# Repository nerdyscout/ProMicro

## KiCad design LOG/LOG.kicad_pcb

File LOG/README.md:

# ProMicro_LOG 
This module can be mounted to an [Arduino Pro Mini](https://www.sparkfun.com/products/11113), [Arduino Nano](https://store.arduino.cc/arduino-nano), [Sparkfun Pro Micro](https://www.sparkfun.com/products/12587), or any other pincompatible MCU running with 3.3V. Depending on assembly it provides a RTC and/or µSD card slot.

## Documentation 
All files can be found on [Github](https://github.com/nerdyscout/ProMicro/tree/master/LOG).

### Schematic

### BoM
  * [interactiveHTMLBoM](https://nerdyscout.github.io/ProMicro/LOG/docs/bom/LOG-ibom.html)
  * [octopart](pcb/docs/bom/LOG-bom_octopart.csv)

## Hardware 
### Layout

### Gerbers
can be found within the Github [repository](pcb/gerbers).

## Code  (unless otherwise stated)
  * [SD CardInfo](examples/CardInfo/CardInfo.ino) 
  * [RTC SetAlarm](examples/SetAlarm/SetAlarm.ino)
  * [OpenLog](examples/OpenLog/OpenLog.ino)

Openlog seems to be tied to Serial0, but ProMicro does use Serial0 for USB and Serial1 internal. Therefore these can not easily be used.

## external
### Links
  * [hackaday.io](https://hackaday.io/project/171898-promicro)

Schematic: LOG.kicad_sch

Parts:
A1: Sparkfun_Pro_Micro
C1: 100n; C_0603_1608Metric
D1: LED; LED_0603_1608Metric
J1: Micro_SD_Card_Det; microSD_HC_Molex_104031-0811
JP1, JP2: Jumper_NO_Small; SolderJumper-2_P1.3mm_Open_RoundedPad1.0x1.5mm
JP3: SolderJumper_3_Bridged12; SolderJumper-3_P1.3mm_Bridged12_RoundedPad1.0x1.5mm_NumberL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
LOGO1: Logo_Open_Hardware_Small; OSHW-Symbol_6.7x6mm_SilkScreen
R1, R2, R3, R5, R6: 4k7; R_0603_1608Metric
R4: 1k; R_0603_1608Metric
TP1: VBAT; TestPoint_THTPad_D2.0mm_Drill1.0mm
U1: DS3231MZ; SOIC-8_3.9x4.9mm_P1.27mm

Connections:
+3V3: A1.21 (VCC), C1.1, J1.4, R2.1, R3.1, R5.1, R6.1, U1.2 (VCC)
BTN: A1.9 (D6/A7), R1.2
CIPO: A1.15 (MISO/D14), J1.7
COPI: A1.14 (MOSI/D16), J1.3
CS: J1.2, JP3.2 (C)
CS0: A1.13 (CS/D10), JP3.3 (B)
CS1: A1.12 (D9/A9), JP3.1 (A)
GND: A1.3 (GND), A1.4 (GND), A1.23 (GND), C1.2, D1.1 (K), J1.6, J1.10, J1.11, U1.5 (GND)
INT: A1.10 (D7), JP2.2 (B)
unnamed: D1.2 (A), R4.2
unnamed: J1.9, R1.1
unnamed: JP1.1 (A), R3.2, U1.1 (32KHZ)
unnamed: JP2.1 (A), R2.2, U1.3 (~INT/SQW)
unnamed: TP1.1, U1.6 (VBAT)
PWM: A1.8 (D5), JP1.2 (B)
SCK: A1.16 (SCK/D15), J1.5, R4.1
SCL: A1.6 (SCL/D3), R5.2, U1.8 (SCL)
SDA: A1.5 (SDA/D2), R6.2, U1.7 (SDA)
~RST: A1.22 (~RESET), U1.4 (~RST)

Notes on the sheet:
TDI
TD0
TMS
TCK

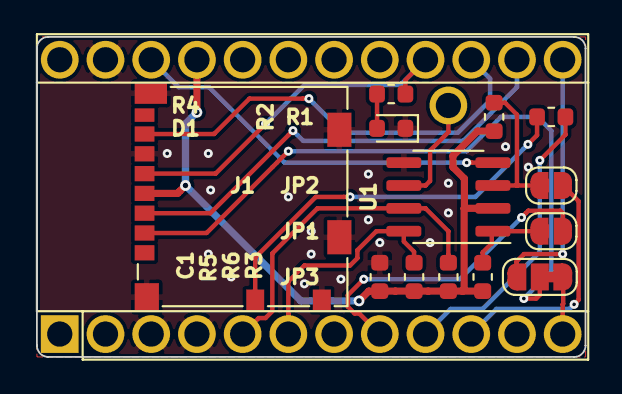
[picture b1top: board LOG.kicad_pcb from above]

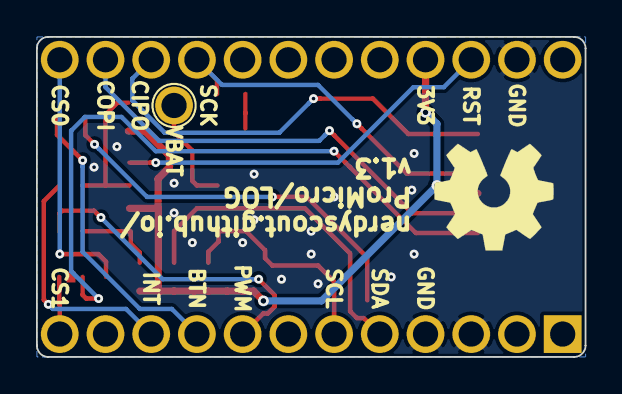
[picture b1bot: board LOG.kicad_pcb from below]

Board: 2 copper layers, 30.5 x 17.8 mm, 16 parts (2 on the bottom side), 19 nets.

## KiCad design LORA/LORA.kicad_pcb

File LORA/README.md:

:warning:
PCB currently not working! most likely some issue in the HF circuit.

# ProMicro_LORA 
This module can be mounted to an [Arduino Pro Mini](https://www.sparkfun.com/products/11113), [Arduino Nano](https://store.arduino.cc/arduino-nano), [Sparkfun Pro Micro](https://www.sparkfun.com/products/12587), or any other pincompatible MCU running with 3.3V. Manufacturing this PCB with 0.8mm thickness allows to mount a GPS module onto its back.

## Documentation 
All files can be found on [Github](https://github.com/nerdyscout/ProMicro/tree/master/LORA).

### Schematic

### BoM
  * [interactiveHTMLBoM](https://nerdyscout.github.io/ProMicro/LORA/docs/bom/LORA-ibom.html)
  * [octopart](pcb/docs/bom/LORA-bom_octopart.csv)

## Hardware 
### Layout

### Gerbers
can be found within the Github [repository](pcb/gerbers).

## Code  (unless otherwise stated)
 * [SX1276](examples/SX1276/SX1276.ino)

## external
### Links
  * [hackaday.io](https://hackaday.io/project/171898-promicro)

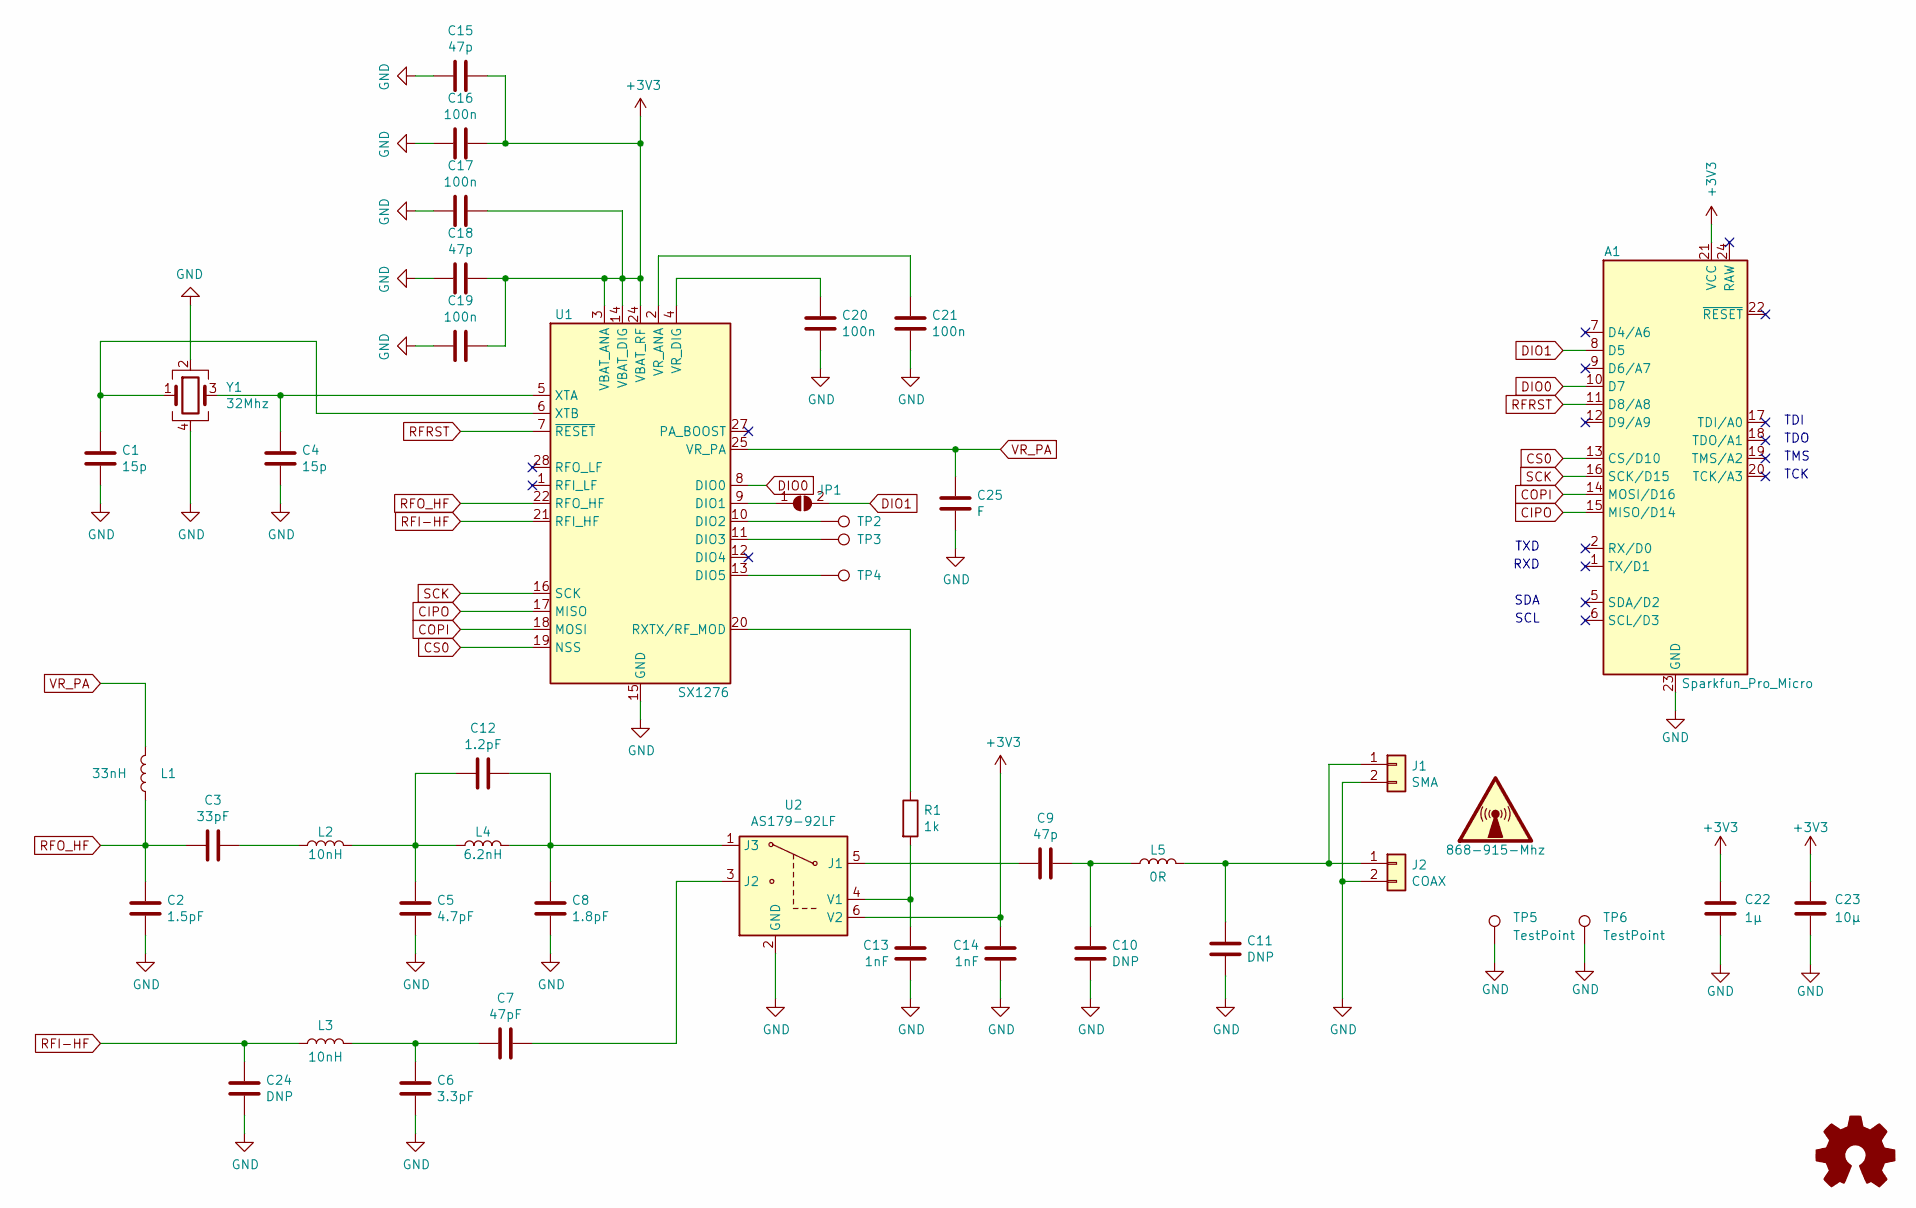
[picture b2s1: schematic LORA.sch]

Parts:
A1: Sparkfun_Pro_Micro
C1, C4: 15p; C_0402_1005Metric; MPN 0402CG150J500NT; LCSC# C1548
C2: 1.5pF; C_0402_1005Metric; MPN 0402CG1R5C500NT; LCSC# C1552
C3: 33pF; C_0402_1005Metric; MPN 0402CG330J500NT; LCSC# C1562
C5: 4.7pF; C_0402_1005Metric; MPN 0402CG4R7C500NT; LCSC# C1569
C6: 3.3pF; C_0402_1005Metric; MPN 0402CG3R3C500NT; LCSC# C1565
C7: 47pF; C_0402_1005Metric; MPN 0402CG470J500NT; LCSC# C1567
C8: 1.8pF; C_0402_1005Metric
C9, C15, C18: 47p; C_0402_1005Metric; MPN 0402CG470J500NT; LCSC# C1567
C10, C11, C24: DNP; C_0402_1005Metric
C12: 1.2pF; C_0402_1005Metric; MPN CL05C1R2BB5NNNC; LCSC# C159809
C13, C14: 1nF; C_0402_1005Metric; MPN 0402B102K500NT; LCSC# C1523
C16, C17, C19, C20, C21: 100n; C_0402_1005Metric; MPN CL05B104KO5NNNC; LCSC# C1525
C22: 1µ; C_0402_1005Metric; MPN CL05A105KA5NQNC; LCSC# C52923
C23: 10µ; C_0603_1608Metric; MPN CL05A106MQ5NUNC; LCSC# C15525
C25: F; C_0402_1005Metric
J1: SMA; U.FL_Hirose_U.FL-R-SMT-1_Vertical
J2: COAX; SMA_Samtec_SMA-J-P-H-ST-EM1_EdgeMount
JP1: SolderJumper_2_Open; SolderJumper-2_P1.3mm_Open_RoundedPad1.0x1.5mm
L1: 33nH; L_0402_1005Metric; MPN HK100533NJ-T; LCSC# C87193
L2, L3: 10nH; L_0402_1005Metric; MPN SDCL1005C10NJTDF; LCSC# C27147
L4: 6.2nH; L_0402_1005Metric; MPN MLG1005S6N2ST000; LCSC# C87534
L5: 0R; L_0402_1005Metric; MPN 0402WGF0000TCE; LCSC# C17168
LOGO1: Logo_Open_Hardware_Small; OSHW-Symbol_6.7x6mm_SilkScreen
R1: 1k; R_0402_1005Metric; MPN 0402WGF1001TCE; LCSC# C11702
TP2: DIO2; TestPoint_Pad_D1.0mm
TP3: DIO3; TestPoint_Pad_D1.0mm
TP4: DIO5; TestPoint_Pad_D1.0mm
TP5, TP6: TestPoint; TestPoint_Pad_1.5x1.5mm
U1: SX1276; QFN-28-1EP_6x6mm_P0.65mm_EP4.8x4.8mm
U2: AS179-92LF; SOT-363_SC-70-6; MPN AS179-92LF; LCSC# C83422
Y1: 32Mhz; Crystal_SMD_SeikoEpson_FA238V-4Pin_3.2x2.5mm; MPN X1E000021016300; LCSC# C91742

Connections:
+3V3: A1.21 (VCC), C14.1, C15.1, C16.2, C17.2, C18.1, C19.2, C22.1, C23.1, U1.3 (VBAT_ANA), U1.14 (VBAT_DIG), U1.24 (VBAT_RF), U2.6 (V2)
CIPO: A1.15 (MISO/D14), U1.17 (MISO)
COPI: A1.14 (MOSI/D16), U1.18 (MOSI)
CS0: A1.13 (CS/D10), U1.19 (NSS)
DIO0: A1.10 (D7), U1.8 (DIO0)
DIO1: A1.8 (D5), JP1.2 (B)
GND: A1.3 (GND), A1.4 (GND), A1.23 (GND), C1.2, C2.1, C4.2, C5.2, C6.2, C8.2, C10.2, C11.2, C13.2, C14.2, C15.2, C16.1, C17.1, C18.2, C19.1, C20.2, C21.2, C22.2, C23.2, C24.2, C25.2, J1.2, J2.2, TP5.1, TP6.1, U1.15 (GND), U1.23 (GND), U1.26 (GND), U1.29 (GND), U2.2 (GND), Y1.2, Y1.4
unnamed: C3.1, L2.1
unnamed: C6.1, C7.2, L3.2
unnamed: C9.1, C10.1, L5.1
unnamed: C5.1, C12.2, L2.2, L4.1
unnamed: C11.1, J1.1, J2.1, L5.2
unnamed: JP1.1 (A), U1.9 (DIO1)
unnamed: TP2.1, U1.10 (DIO2)
unnamed: TP3.1, U1.11 (DIO3)
unnamed: TP4.1, U1.13 (DIO5)
unnamed: R1.1, U1.20 (RXTX/RF_MOD)
unnamed: C21.1, U1.2 (VR_ANA)
unnamed: C20.1, U1.4 (VR_DIG)
unnamed: C4.1, U1.5 (XTA), Y1.3
unnamed: C1.1, U1.6 (XTB), Y1.1
unnamed: C9.2, U2.5 (J1)
unnamed: C7.1, U2.3 (J2)
unnamed: C8.1, C12.1, L4.2, U2.1 (J3)
unnamed: C13.1, R1.2, U2.4 (V1)
RFI-HF: C24.1, L3.1, U1.21 (RFI_HF)
RFO_HF: C2.2, C3.2, L1.1, U1.22 (RFO_HF)
RFRST: A1.11 (D8/A8), U1.7 (~RESET)
SCK: A1.16 (SCK/D15), U1.16 (SCK)
VR_PA: C25.1, L1.2, U1.25 (VR_PA)

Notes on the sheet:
TDI
TDO
TMS
TCK
RXD
TXD
SDA
SCL

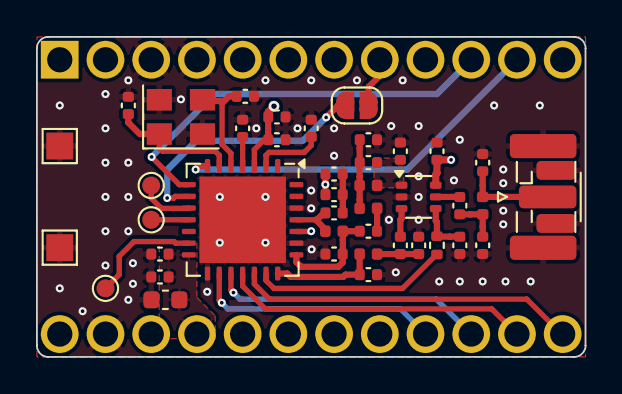
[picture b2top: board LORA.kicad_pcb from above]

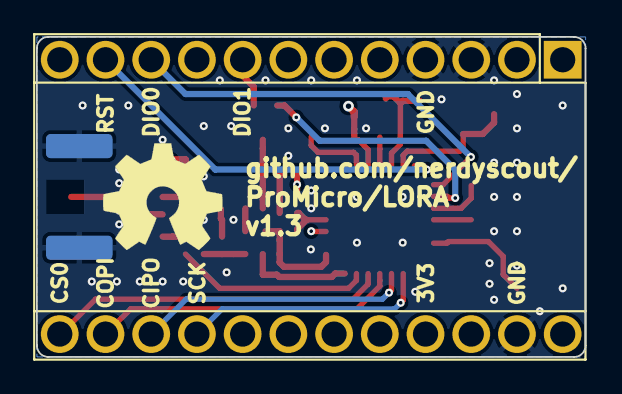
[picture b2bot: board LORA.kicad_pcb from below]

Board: 4 copper layers, 30.5 x 17.8 mm, 44 parts (2 on the bottom side), 30 nets.

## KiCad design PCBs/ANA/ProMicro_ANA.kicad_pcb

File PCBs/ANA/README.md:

# ProMicro_ANA
This module can be mounted to an [Arduino Pro Mini](https://www.sparkfun.com/products/11113), [Arduino Nano](https://store.arduino.cc/arduino-nano), [Sparkfun Pro Micro](https://www.sparkfun.com/products/12587), or any other pincompatible MCU running with 3.3V. Depending on assembly it provides a RTC and/or µSD card slot.

## Documentation
All files can be found on [Github](https://github.com/nerdyscout/ProMicro_ANA).

### Schematic

### Layout

### BoM
  * [interactiveHTMLBoM](https://nerdyscout.github.io/ProMicro_ANA/docs/bom/ProMicro_ANA.html))
  * [kicost](docs/bom/ProMicro_ANA.xlsx)
  * [csv](docs/bom/ProMicro_ANA.csv)

## Gerbers
can be found within the Github [repository](https://github.com/nerdyscout/ProMicro_ANA/tree/master/gerbers).

## Code
| | 1 | 2 |
| --- | --- | --- |
| Sparkfun ProMicro | [a](l) | [b](l) |
| Arduino Mini | [a](l)<br>[c](l) | [b](l) |

## Links
  * [hackaday.io](https://hackaday.io/project/171898-promicro)

## License
Copyright Stefan Herold 2020

This documentation describes Open Hardware and is licensed under the CERN OHL v.1.2.

You may redistribute and modify this documentation under the terms of the CERN OHL v.1.2. (http://ohwr.org/cernohl). This documentation is distributed WITHOUT ANY EXPRESS OR IMPLIED WARRANTY, INCLUDING OF MERCHANTABILITY, SATISFACTORY QUALITY AND FITNESS FOR A PARTICULAR PURPOSE. Please see the CERN OHL v.1.2 for applicable conditions

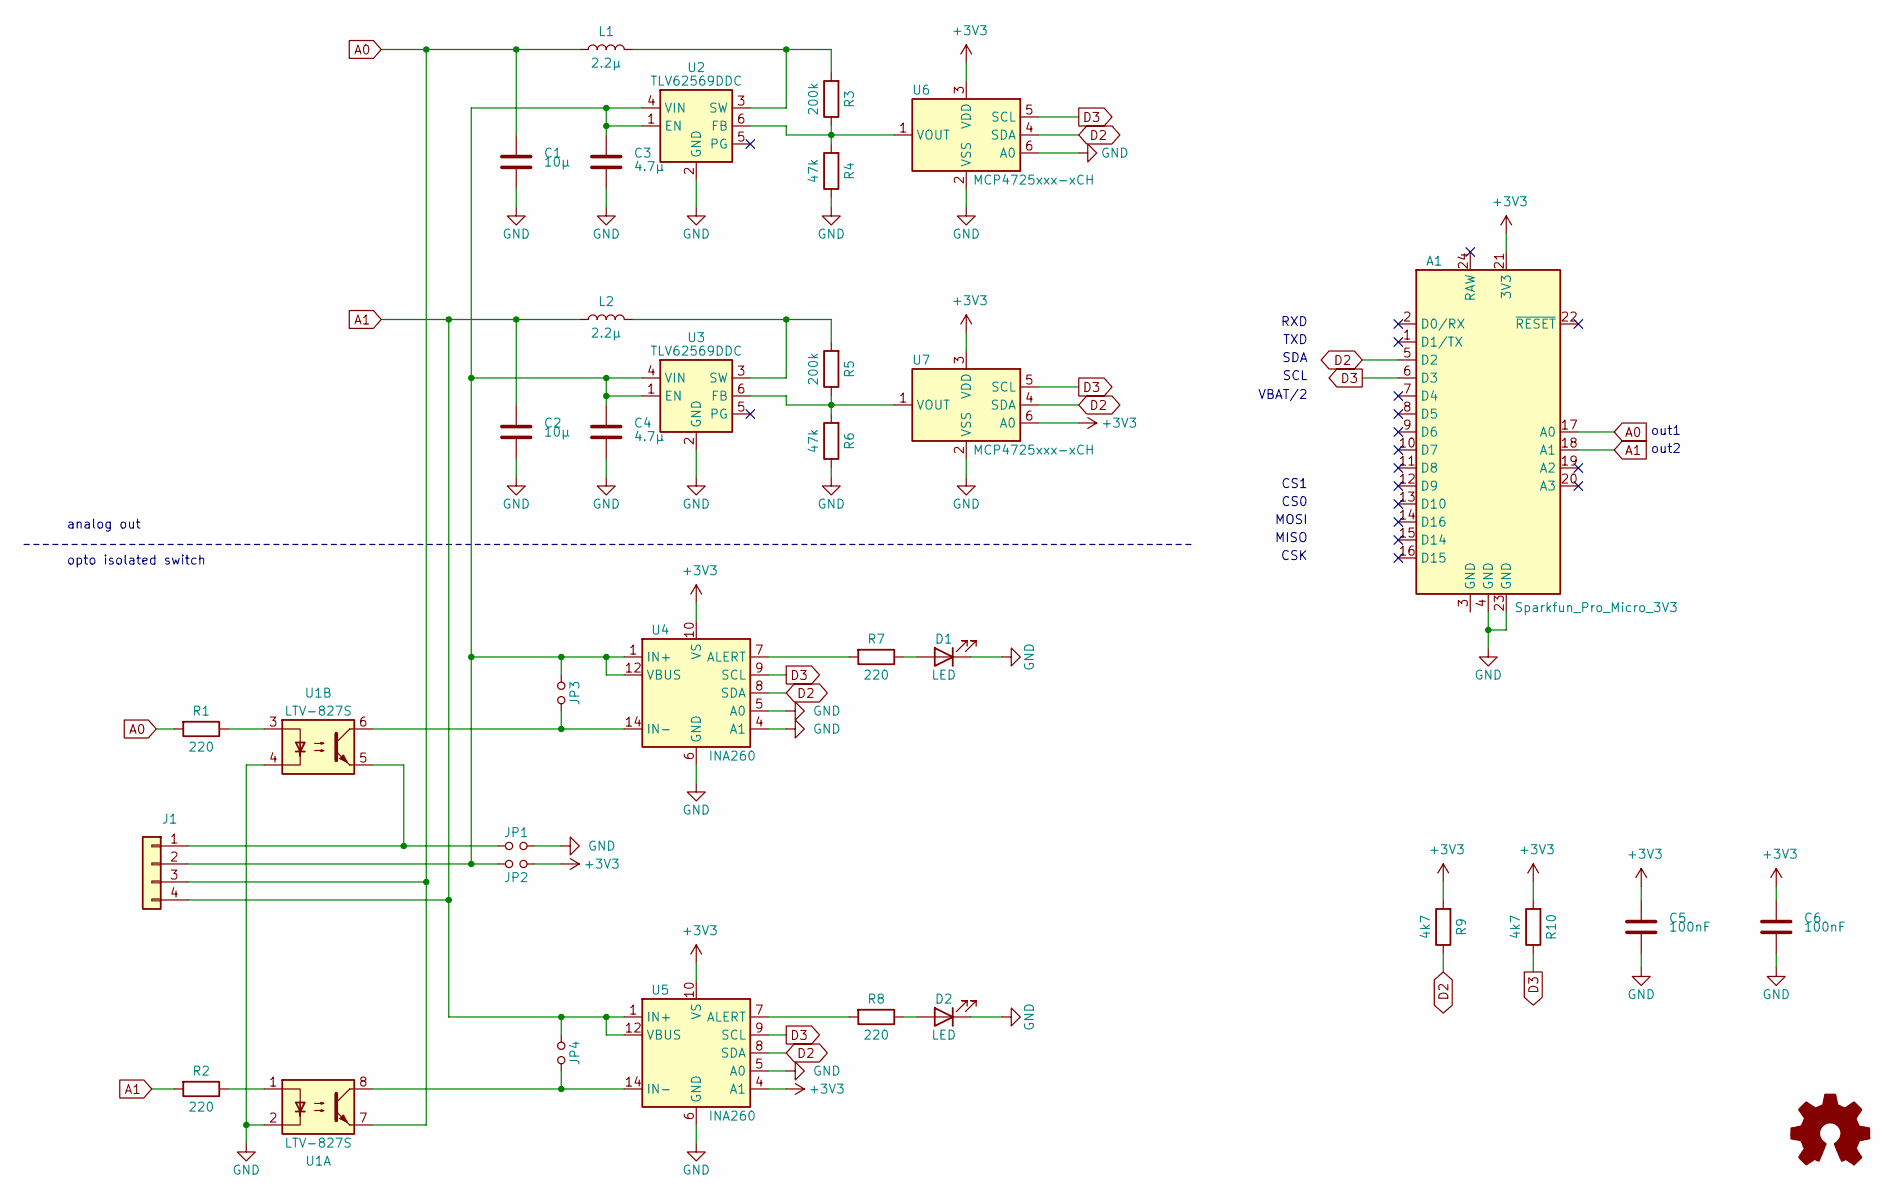
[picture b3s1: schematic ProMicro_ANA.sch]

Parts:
A1: Sparkfun_Pro_Micro_3V3; Sparkfun_Pro_Micro
C1, C2: 10µ; C_0603_1608Metric
C3, C4: 4.7µ; C_0603_1608Metric
C5, C6: 100nF; C_0603_1608Metric
D1, D2: LED; LED_0603_1608Metric
J1: Conn_01x04; TerminalBlock_Phoenix_MPT-0,5-4-2.54_1x04_P2.54mm_Horizontal
JP1, JP2, JP3, JP4: Jumper_NO_Small; SolderJumper-2_P1.3mm_Open_RoundedPad1.0x1.5mm
L1, L2: 2.2µ; L_Bourns-SRN4018
LOGO1: Logo_Open_Hardware_Small; OSHW-Symbol_6.7x6mm_SilkScreen
R1, R2, R7, R8: 220; R_0603_1608Metric
R3, R5: 200k; R_0603_1608Metric
R4, R6: 47k; R_0603_1608Metric
R9, R10: 4k7; R_0603_1608Metric
U1: LTV-827S; SMDIP-8_W9.53mm
U2, U3: TLV62569DDC; SOT-23-6
U4, U5: INA260; TSSOP-16_4.4x5mm_P0.65mm
U6, U7: MCP4725xxx-xCH; SOT-23-6

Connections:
+3V3: A1.21 (3V3), C5.1, C6.1, JP2.2, R9.2, R10.2, U4.10 (VS), U5.4 (A1), U5.10 (VS), U6.3 (VDD), U7.3 (VDD), U7.6 (A0)
A0: A1.17 (A0), C1.1, J1.3, L1.1, R1.2, U1.7
A1: A1.18 (A1), C2.1, J1.4, JP4.1, L2.1, R2.2, U5.1 (IN+), U5.2 (IN+), U5.3 (IN+), U5.12 (VBUS)
D2: A1.5 (D2), R9.1, U4.8 (SDA), U5.8 (SDA), U6.4 (SDA), U7.4 (SDA)
D3: A1.6 (D3), R10.1, U4.9 (SCL), U5.9 (SCL), U6.5 (SCL), U7.5 (SCL)
GND: A1.4 (GND), A1.23 (GND), C1.2, C2.2, C3.2, C4.2, C5.2, C6.2, D1.1 (K), D2.1 (K), JP1.2, R4.1, R6.1, U1.2, U1.4, U2.2 (GND), U3.2 (GND), U4.4 (A1), U4.5 (A0), U4.6 (GND), U4.11 (GND), U5.5 (A0), U5.6 (GND), U5.11 (GND), U6.2 (VSS), U6.6 (A0), U7.2 (VSS)
unnamed: C3.1, C4.1, J1.2, JP2.1, JP3.1, U2.1 (EN), U2.4 (VIN), U3.1 (EN), U3.4 (VIN), U4.1 (IN+), U4.2 (IN+), U4.3 (IN+), U4.12 (VBUS)
unnamed: D1.2 (A), R7.1
unnamed: D2.2 (A), R8.1
unnamed: J1.1, JP1.1, U1.5
unnamed: JP3.2, U1.6, U4.14 (IN-), U4.15 (IN-), U4.16 (IN-)
unnamed: JP4.2, U1.8, U5.14 (IN-), U5.15 (IN-), U5.16 (IN-)
unnamed: L1.2, R3.2, U2.3 (SW)
unnamed: L2.2, R5.2, U3.3 (SW)
unnamed: R1.1, U1.3
unnamed: R2.1, U1.1
unnamed: R3.1, R4.2, U2.6 (FB), U6.1 (VOUT)
unnamed: R5.1, R6.2, U3.6 (FB), U7.1 (VOUT)
unnamed: R7.2, U4.7 (ALERT)
unnamed: R8.2, U5.7 (ALERT)

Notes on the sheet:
out1
out2
opto isolated switch
analog out
SCL
SDA
TXD
RXD
CSK
MISO
MOSI
CS0
CS1
VBAT/2

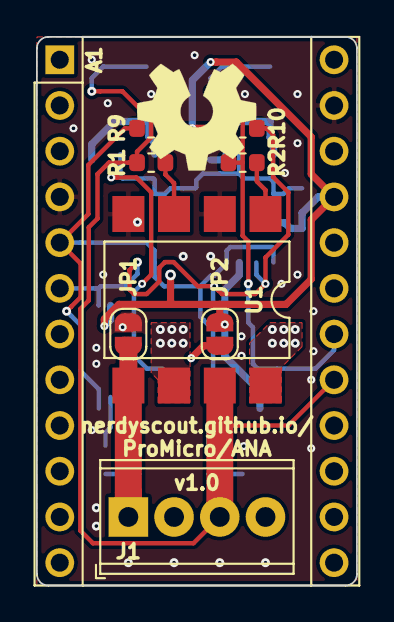
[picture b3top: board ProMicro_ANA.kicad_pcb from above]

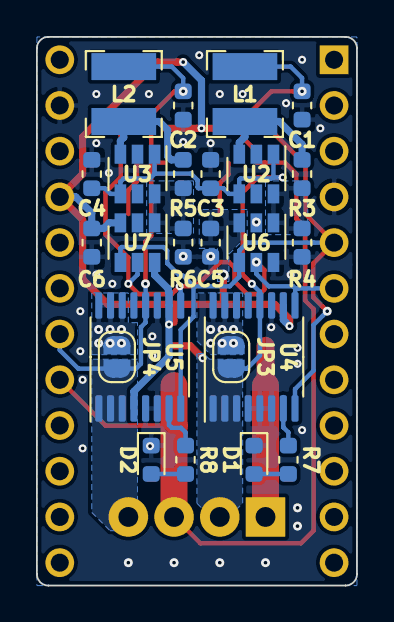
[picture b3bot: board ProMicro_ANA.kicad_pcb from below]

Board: 2 copper layers, 17.8 x 30.5 mm, 34 parts (24 on the bottom side), 20 nets.

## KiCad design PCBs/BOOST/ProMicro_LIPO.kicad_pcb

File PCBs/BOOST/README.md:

# ProMicro_LIPO
This module can be mounted, back on back, to any [Arduino Pro Mini](https://www.sparkfun.com/products/11113), [Arduino Nano](https://store.arduino.cc/arduino-nano) or [Sparkfun Pro Micro](https://www.sparkfun.com/products/12587) running with 3.3V. While the controller gets externally powered the LiPo battery is charging, removing the cable the device keeps running on battery.

## Documentation
All files can be found on [Github](https://github.com/nerdyscout/ProMicro_LIPO).

### Schematic

### Layout

### BoM
  * [interactiveHTMLBoM](https://nerdyscout.github.io/ProMicro_LIPO/docs/BOM/ProMicro_LIPO.html)
  * [kicost](docs/BOM/ProMicro_LIPO.xlsx)
  * [csv](docs/BOM/ProMicro_LIPO.csv)

## Gerbers
can be found within the Github [repository](gerbers).

## Code
  * [Arduino Micro 3V3](examples/Arduino_Micro_LIPO/Arduino_Micro_LIPO.ino)
  * [Arduino Nano 3V3](examples/Arduino_Nano_LIPO/Arduino_Nano_LIPO.ino)
  * [Sparkfun Pro Micro 3V3](examples/Sparkfun_ProMicro_LIPO/Sparkfun_ProMicro_LIPO.ino)

## Links
  * [hackaday.io](https://hackaday.io/project/171898-promicro)

## Credits
  * [Adafruit PowerBoost 500 Basic](https://learn.adafruit.com/adafruit-powerboost)

## License
Copyright Stefan Herold 2020

This documentation describes Open Hardware and is licensed under the CERN OHL v.1.2.

You may redistribute and modify this documentation under the terms of the CERN OHL v.1.2. (http://ohwr.org/cernohl). This documentation is distributed WITHOUT ANY EXPRESS OR IMPLIED WARRANTY, INCLUDING OF MERCHANTABILITY, SATISFACTORY QUALITY AND FITNESS FOR A PARTICULAR PURPOSE. Please see the CERN OHL v.1.2 for applicable conditions

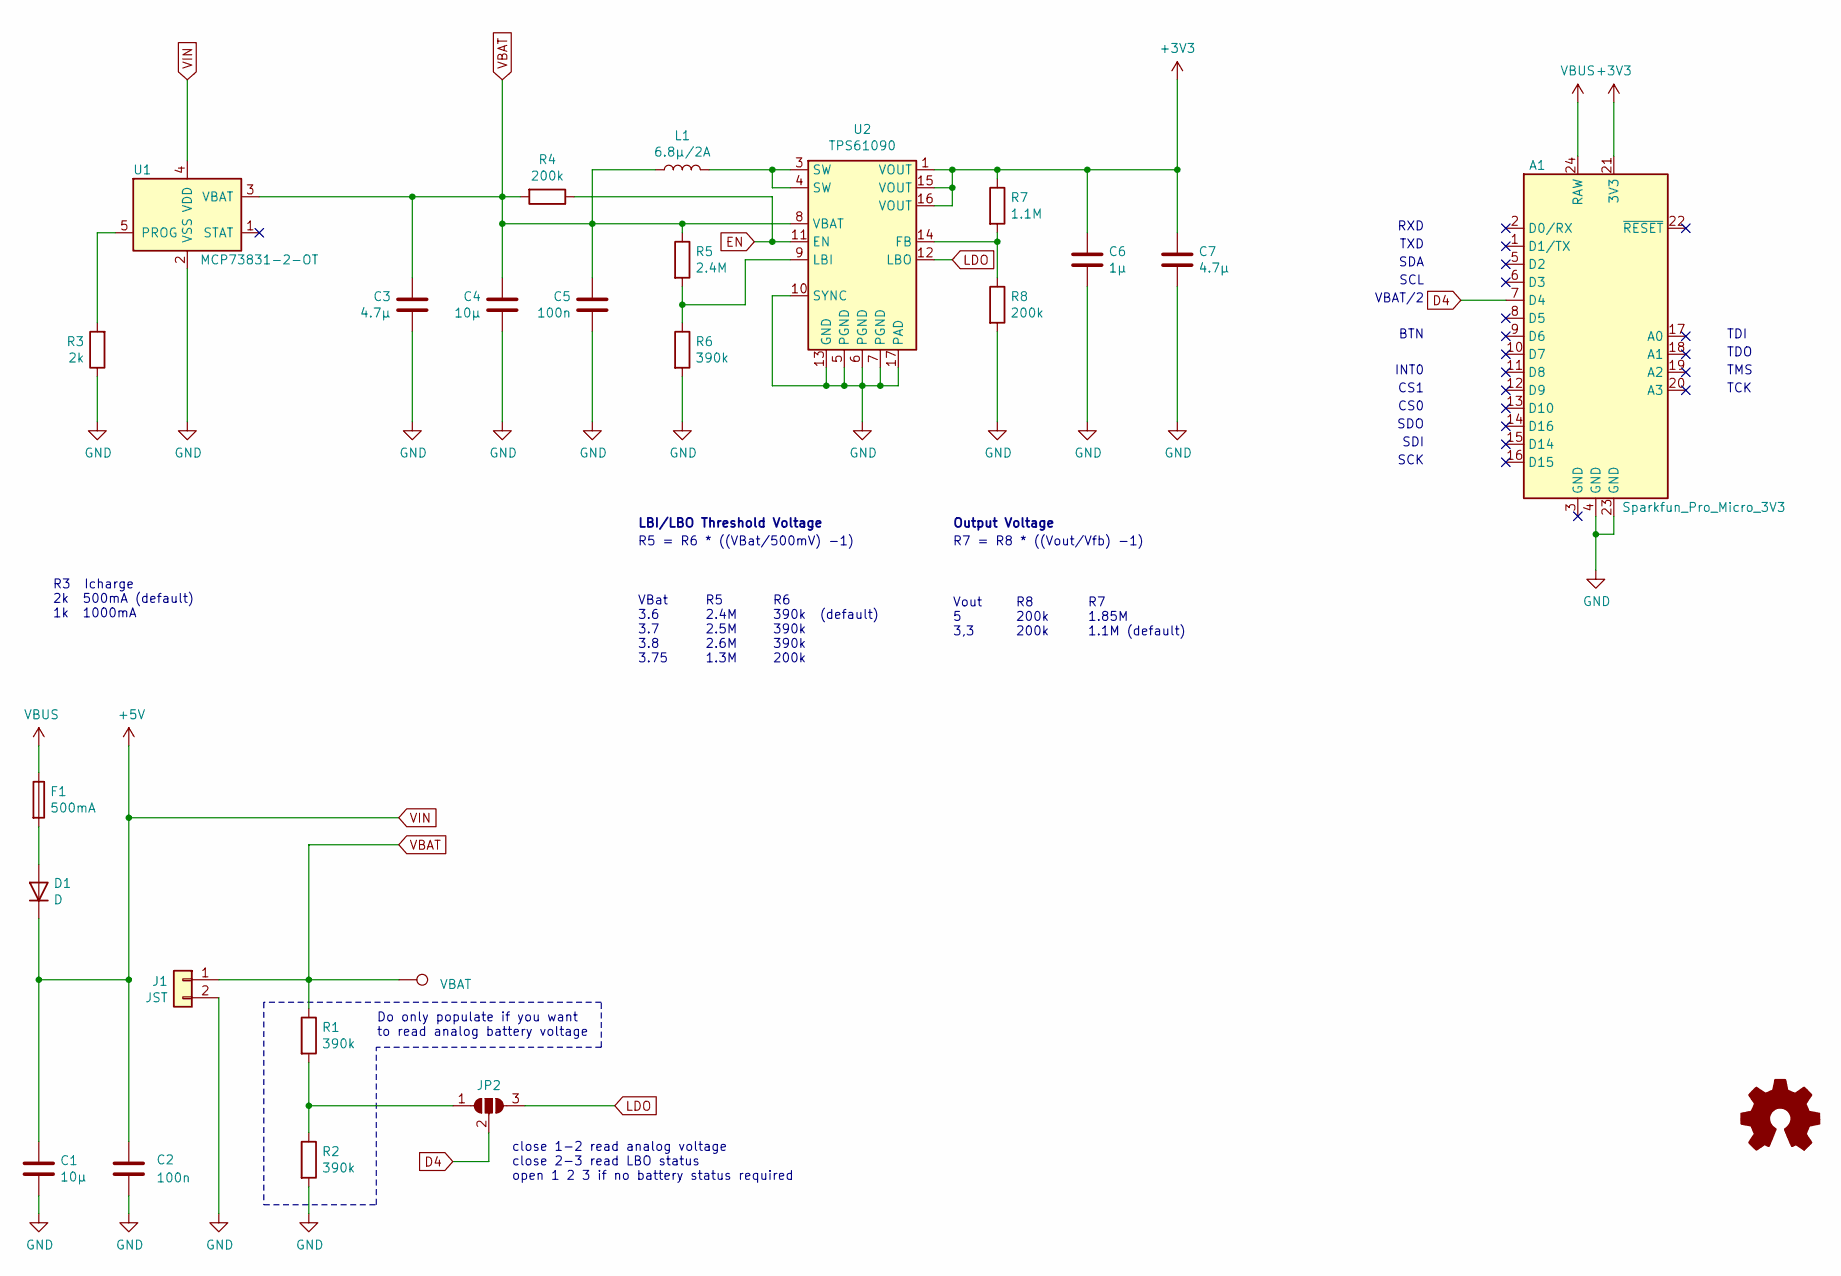
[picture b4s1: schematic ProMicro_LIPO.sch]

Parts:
A1: Sparkfun_Pro_Micro_3V3; Sparkfun_Pro_Micro
C1, C4: 10µ; C_0603_1608Metric; LCSC# C19702
C2, C5: 100n; C_0603_1608Metric; LCSC# C14663
C3, C7: 4.7µ; C_0603_1608Metric; LCSC# C19666
C6: 1µ; C_0603_1608Metric; LCSC# C15849
D1: D; D_0603_1608Metric
F1: 500mA; Fuse_0603_1608Metric; LCSC# C135323
J1: JST; JST_PH_S2B-PH-SM4-TB_1x02-1MP_P2.00mm_Horizontal
JP2: SolderJumper_3_Open; SolderJumper-3_P1.3mm_Open_RoundedPad1.0x1.5mm
L1: 6.8µ/2A; L_Bourns_SRN6045TA; LCSC# C354631
LOGO1: Logo_Open_Hardware_Small; OSHW-Symbol_6.7x6mm_SilkScreen
R1, R2, R6: 390k; R_0603_1608Metric; LCSC# C23150
R3: 2k; R_0603_1608Metric; LCSC# C22975
R4, R8: 200k; R_0603_1608Metric; LCSC# C25811
R5: 2.4M; R_0603_1608Metric; LCSC# C367738
R7: 1.1M; R_0603_1608Metric; LCSC# C169875
TP1: VBAT; TestPoint_THTPad_D2.0mm_Drill1.0mm
U1: MCP73831-2-OT; SOT-23-5; LCSC# C14879
U2: TPS61090; Texas_S-PVQFN-N16_EP2.7x2.7mm_ThermalVias; LCSC# C206167

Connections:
+3V3: A1.21 (3V3), C6.1, C7.1, R7.1, U2.1 (VOUT), U2.15 (VOUT), U2.16 (VOUT)
D4: A1.7 (D4), JP2.2 (C)
EN: R4.1, U2.11 (EN)
GND: A1.4 (GND), A1.23 (GND), C1.2, C2.1, C3.1, C4.1, C5.2, C6.2, C7.2, J1.2, R2.2, R3.1, R6.2, R8.2, U1.2 (VSS), U2.5 (PGND), U2.6 (PGND), U2.7 (PGND), U2.10 (SYNC), U2.13 (GND), U2.17 (PAD)
LDO: JP2.3 (B), U2.12 (LBO)
unnamed: D1.2 (A), F1.2
unnamed: JP2.1 (A), R1.2, R2.1
unnamed: L1.2, U2.3 (SW), U2.4 (SW)
unnamed: R3.2, U1.5 (PROG)
unnamed: R5.2, R6.1, U2.9 (LBI)
unnamed: R7.2, R8.1, U2.14 (FB)
VBAT: C3.2, C4.2, C5.1, J1.1, L1.1, R1.1, R4.2, R5.1, TP1.1, U1.3 (VBAT), U2.8 (VBAT)
VBUS: A1.24 (RAW), F1.1
VIN: C1.1, C2.2, D1.1 (K), U1.4 (VDD)

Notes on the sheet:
VBAT/2
R3 Icharge 2k 500mA (default) 1k 1000mA
LBI/LBO Threshold Voltage
R5 = R6 * ((VBat/500mV) -1)
VBat 3.6 3.7 3.8 3.75
Output Voltage
R7 = R8 * ((Vout/Vfb) -1)
Vout 5 3,3
R5 2.4M 2.5M 2.6M 1.3M
R6 390k (default) 390k 390k 200k
R8 200k 200k
R7 1.85M 1.1M (default)
Do only populate if you want to read analog battery voltage
RXD
TXD
SDA
SCL
SCK
SDI
SDO
CS0
INT0
TDI
TDO
TMS
TCK
close 1-2 read analog voltage close 2-3 read LBO status open 1 2 3 if no battery status required
CS1
BTN

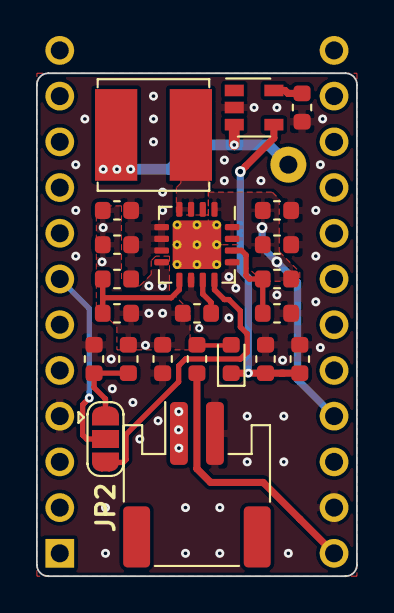
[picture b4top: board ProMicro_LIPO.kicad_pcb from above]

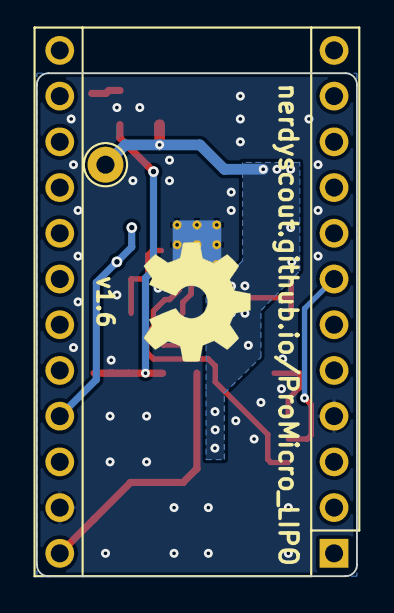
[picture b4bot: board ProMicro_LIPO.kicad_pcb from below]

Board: 2 copper layers, 17.8 x 27.9 mm, 25 parts (3 on the bottom side), 14 nets.

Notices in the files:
LOG/README.md:
Documentation [![CC BY-SA](../img/ccbysa.png)](pcb/docs/LICENSE.TXT):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
PCBs/ANA/ProMicro_ANA.kicad_pcb:
CERN Open Hardware Licence v1.2
